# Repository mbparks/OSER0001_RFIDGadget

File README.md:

View this project on [CADLAB.io](https://cadlab.io/project/2087). 

# Open Source Escape Room Gadget #0001: RFID Puzzle
One of the more nifty puzzles of a great escape room is having to find objects and place them at an exact spot. Say three different candlesticks on a fireplace mantle in a specific order.

RFID tags are a great way to achieve this goal. Embedding RFID tags in the objects and RFID reader at the location the objects are to be placed.

We're building a great solution for just this puzzle concept.

The hardware includes an Arduino Uno, custom Uno shield, and dedicate PCB for 1 to 4 RFID readers to connect. While the software provided is for PN532 RFID readers using SPI communications, the hardware could be used for any RFID reader that communicates back to the microcontroller over SPI. The shield also provides for digital and analog outputs when the puzzle is unlocked. Say to activate a relay. Also an external reset is provided so escape room operators can reset the puzzle from afar.

The software requires just a few small tweaks to change from 1 to 4 RFID readers.

The source code is provided for free on GitHub and an upcoming guidebook will be available on our Gumroad store for around $5 to $10.

This design is provided as-is and no guarantees are offered. Use at your own risk.

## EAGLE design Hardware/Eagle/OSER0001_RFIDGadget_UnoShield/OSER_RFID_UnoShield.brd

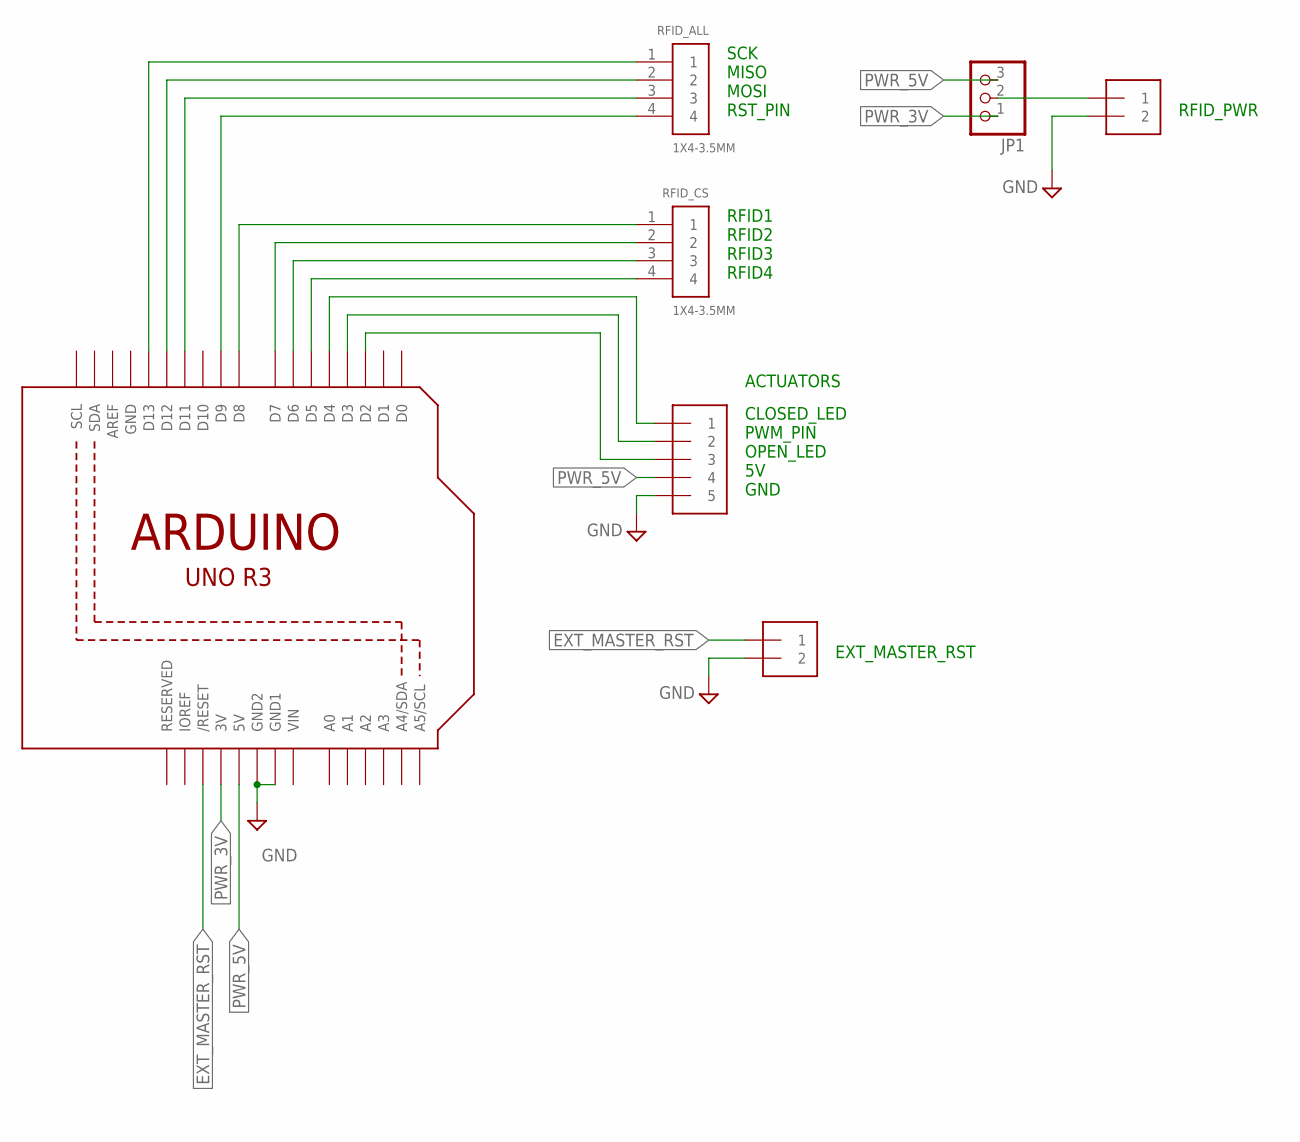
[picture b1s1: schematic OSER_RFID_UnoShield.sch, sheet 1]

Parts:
ACTUATORS: 1X5; 1X05-3.5MM
EXT_RST: 1X2-3.5MM
JP1: PINHD-1X3; 1X03
RFID_ALL: 1X4-3.5MM; 1X04-3.5MM
RFID_CS: 1X4-3.5MM; 1X04-3.5MM
RFID_PWR: 1X2-3.5MM
U1: ARDUINOR3-BPLACE

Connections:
CLOSED_LED: ACTUATORS.1, U1.D4
EXT_MASTER_RST: EXT_RST.1, U1.RESET (/RESET)
GND: ACTUATORS.5, EXT_RST.2, RFID_PWR.2, U1.GND, U1.GND1, U1.GND2
MISO: RFID_ALL.2, U1.D12
MOSI: RFID_ALL.3, U1.D11
unnamed: JP1.2, RFID_PWR.1
OPEN_LED: ACTUATORS.3, U1.D2
PWM_PIN: ACTUATORS.2, U1.D3
PWR_3V: JP1.1, U1.3V
PWR_5V: ACTUATORS.4, JP1.3, U1.5V
RFID2_CS: RFID_CS.2, U1.D7
RFID3_CS: RFID_CS.3, U1.D6
RFID4_CS: RFID_CS.4, U1.D5
RFID_CS1: RFID_CS.1, U1.D8
RST_PIN: RFID_ALL.4, U1.D9
SCK: RFID_ALL.1, U1.D13
VIN: U1.VIN

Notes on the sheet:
SCK MISO MOSI RST_PIN
RFID1 RFID2 RFID3 RFID4
RFID_PWR
EXT_MASTER_RST
CLOSED_LED PWM_PIN OPEN_LED 5V GND
ACTUATORS

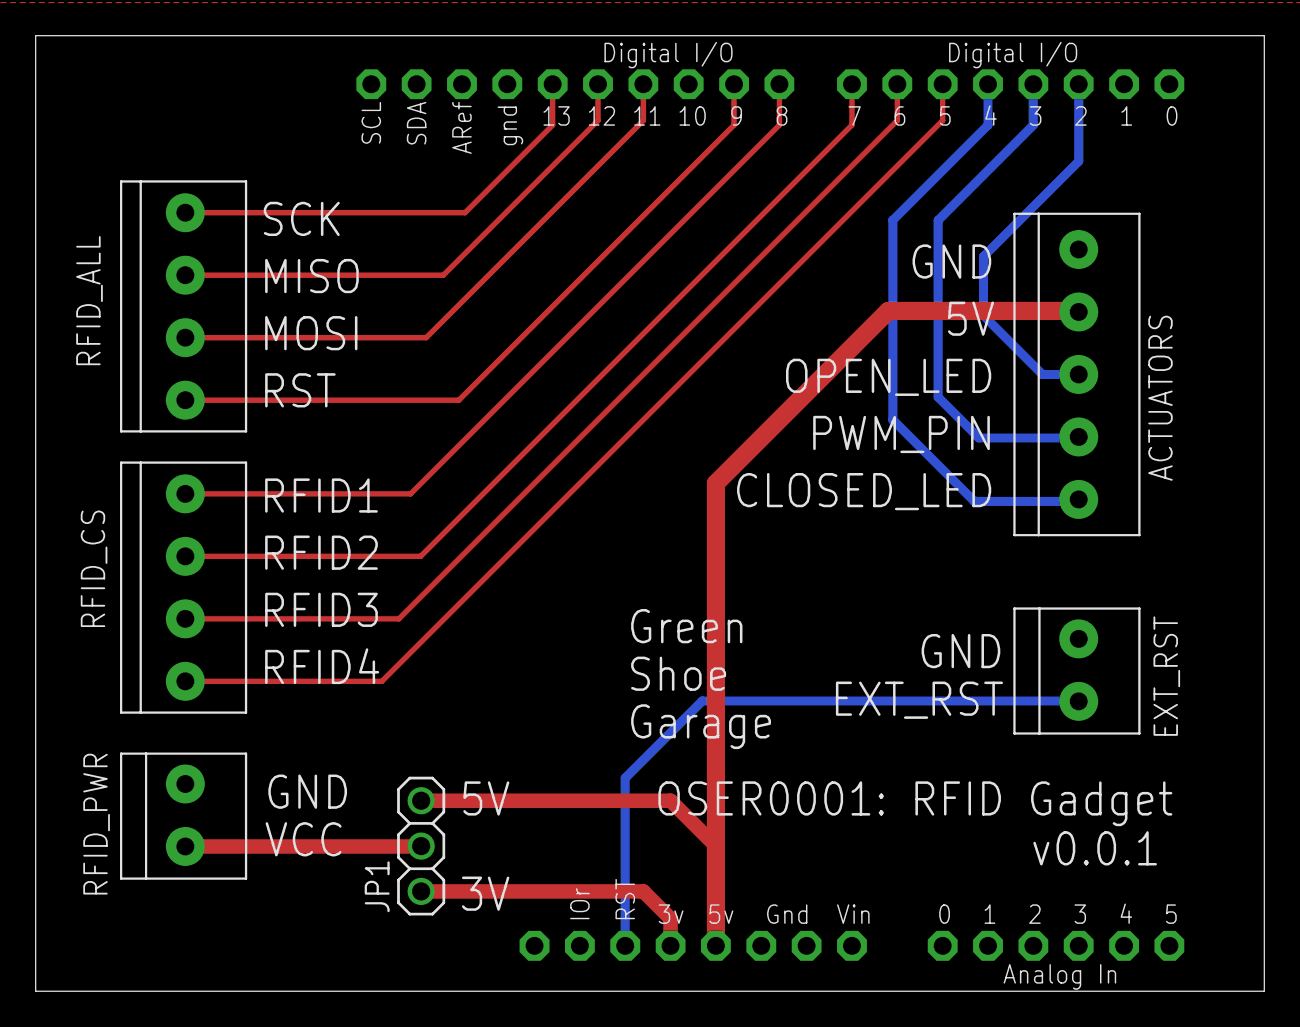
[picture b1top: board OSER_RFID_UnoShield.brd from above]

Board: 2 copper layers, 68.8 x 53.5 mm, 7 parts (0 on the bottom side), 16 nets.

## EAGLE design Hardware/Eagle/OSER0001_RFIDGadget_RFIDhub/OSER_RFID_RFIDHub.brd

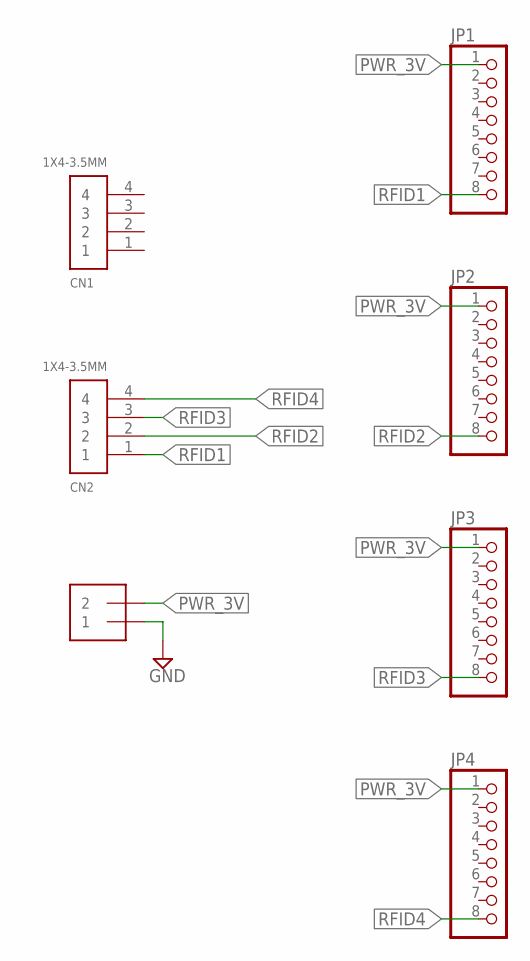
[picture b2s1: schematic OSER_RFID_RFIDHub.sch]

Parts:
CN1, CN2: 1X4-3.5MM; 1X04-3.5MM
J1: 1X2-3.5MM
JP1, JP2, JP3, JP4: PINHD-1X8BIG; 1X08-BIG

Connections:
GND: J1.1
PWR_3V: J1.2, JP1.1, JP2.1, JP3.1, JP4.1
RFID1: CN2.1, JP1.8
RFID2: CN2.2, JP2.8
RFID3: CN2.3, JP3.8
RFID4: CN2.4, JP4.8

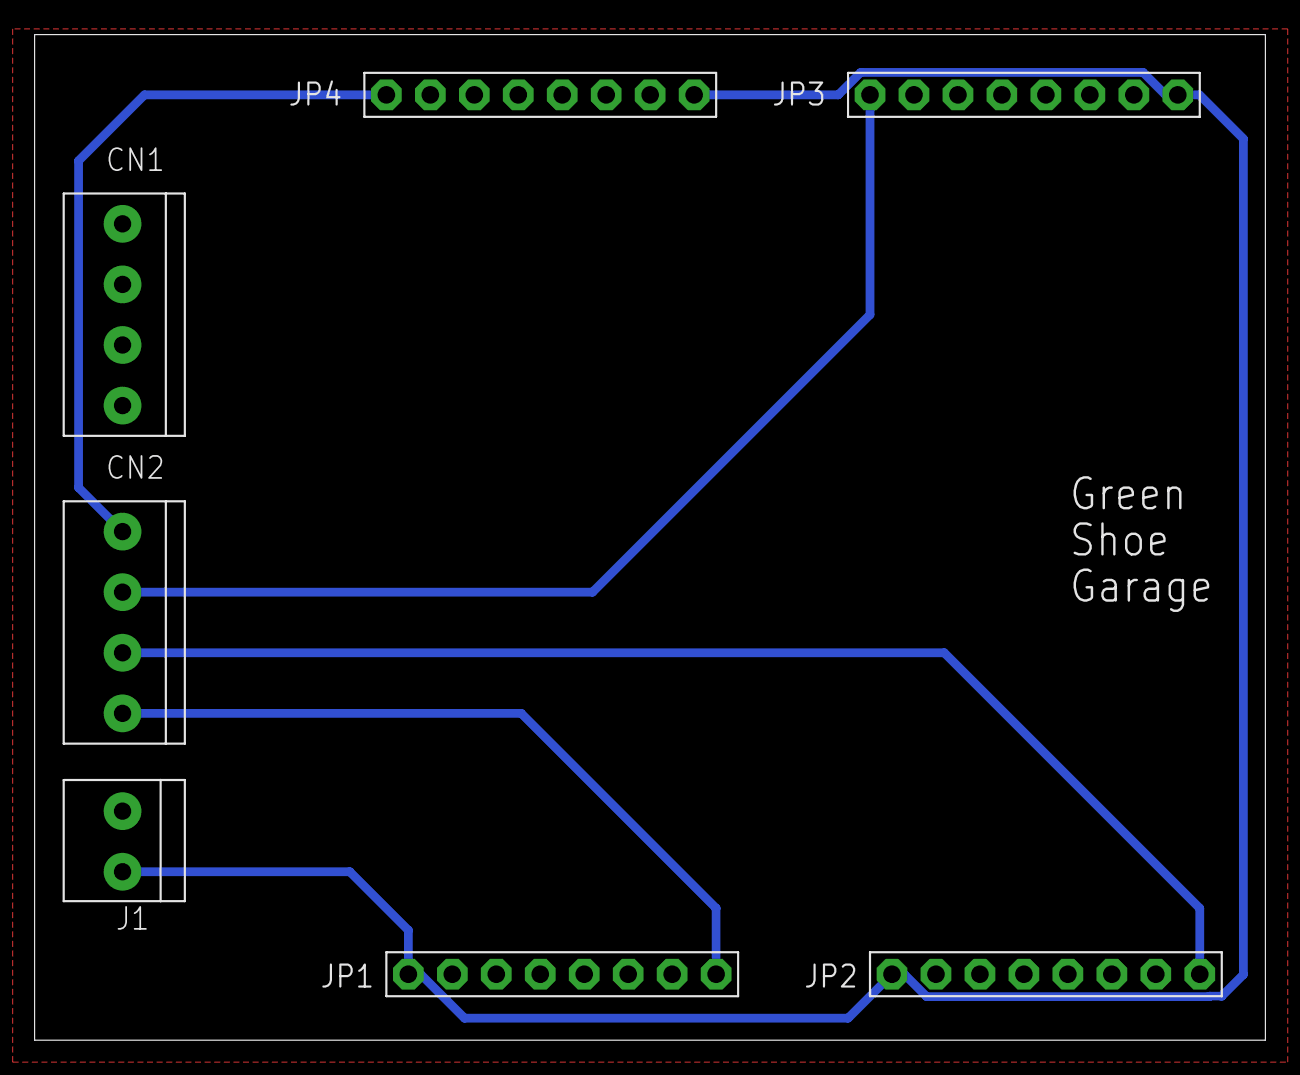
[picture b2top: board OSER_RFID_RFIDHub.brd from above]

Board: 2 copper layers, 71.1 x 58.1 mm, 7 parts (0 on the bottom side), 5 nets.

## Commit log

2019-07-27 init commit
2019-07-27 concept art
2019-07-28 hardware update
2019-07-28 hardware updates
2019-08-30 Changed to 5V for RFID Readers
    Switched to the PN532 RFID reader which uses 5V.
2019-08-30 Update OSER0001_RFID_ArduinoUnoFW.ino
    New code for the PN532 RFID module.
2019-08-31 Changed RFID Power to 5V
2019-08-31 Redefined SPI pins to match PCB layout
2019-08-31 Revised board silkscreen
2019-08-31 Switched to an array of pointers to Adafruit_PN532 objects
2019-08-31 minor tweaks and commenting
2019-09-02 1x3 header pin to allow user select 3V or 5V to RFID reader
2019-09-02 1x3 header for 3V or 5V to the RFID board
2019-09-02 Backlink to CADLAB.io has been added.
2019-09-02 Added PWM and Digital Outputs When Correct RFID Tags presented
2019-09-02 Changed Accepted RFID Tag ID#s to const uint32_t
2019-09-02 minor code cleanup
2019-09-05 changed how to initialize readNfcTags[] array
    Use for loop instead of declaration so user doesn't need to edit code when changing the number of RFID readers used
2019-09-16 uncomment SS3 and SS4 pin declarations
2019-09-16 revised code
2019-09-16 update gitignore
2019-09-16 updarte
2019-09-16 remove hex
2019-09-16 removed vscode
2019-09-16 document code
